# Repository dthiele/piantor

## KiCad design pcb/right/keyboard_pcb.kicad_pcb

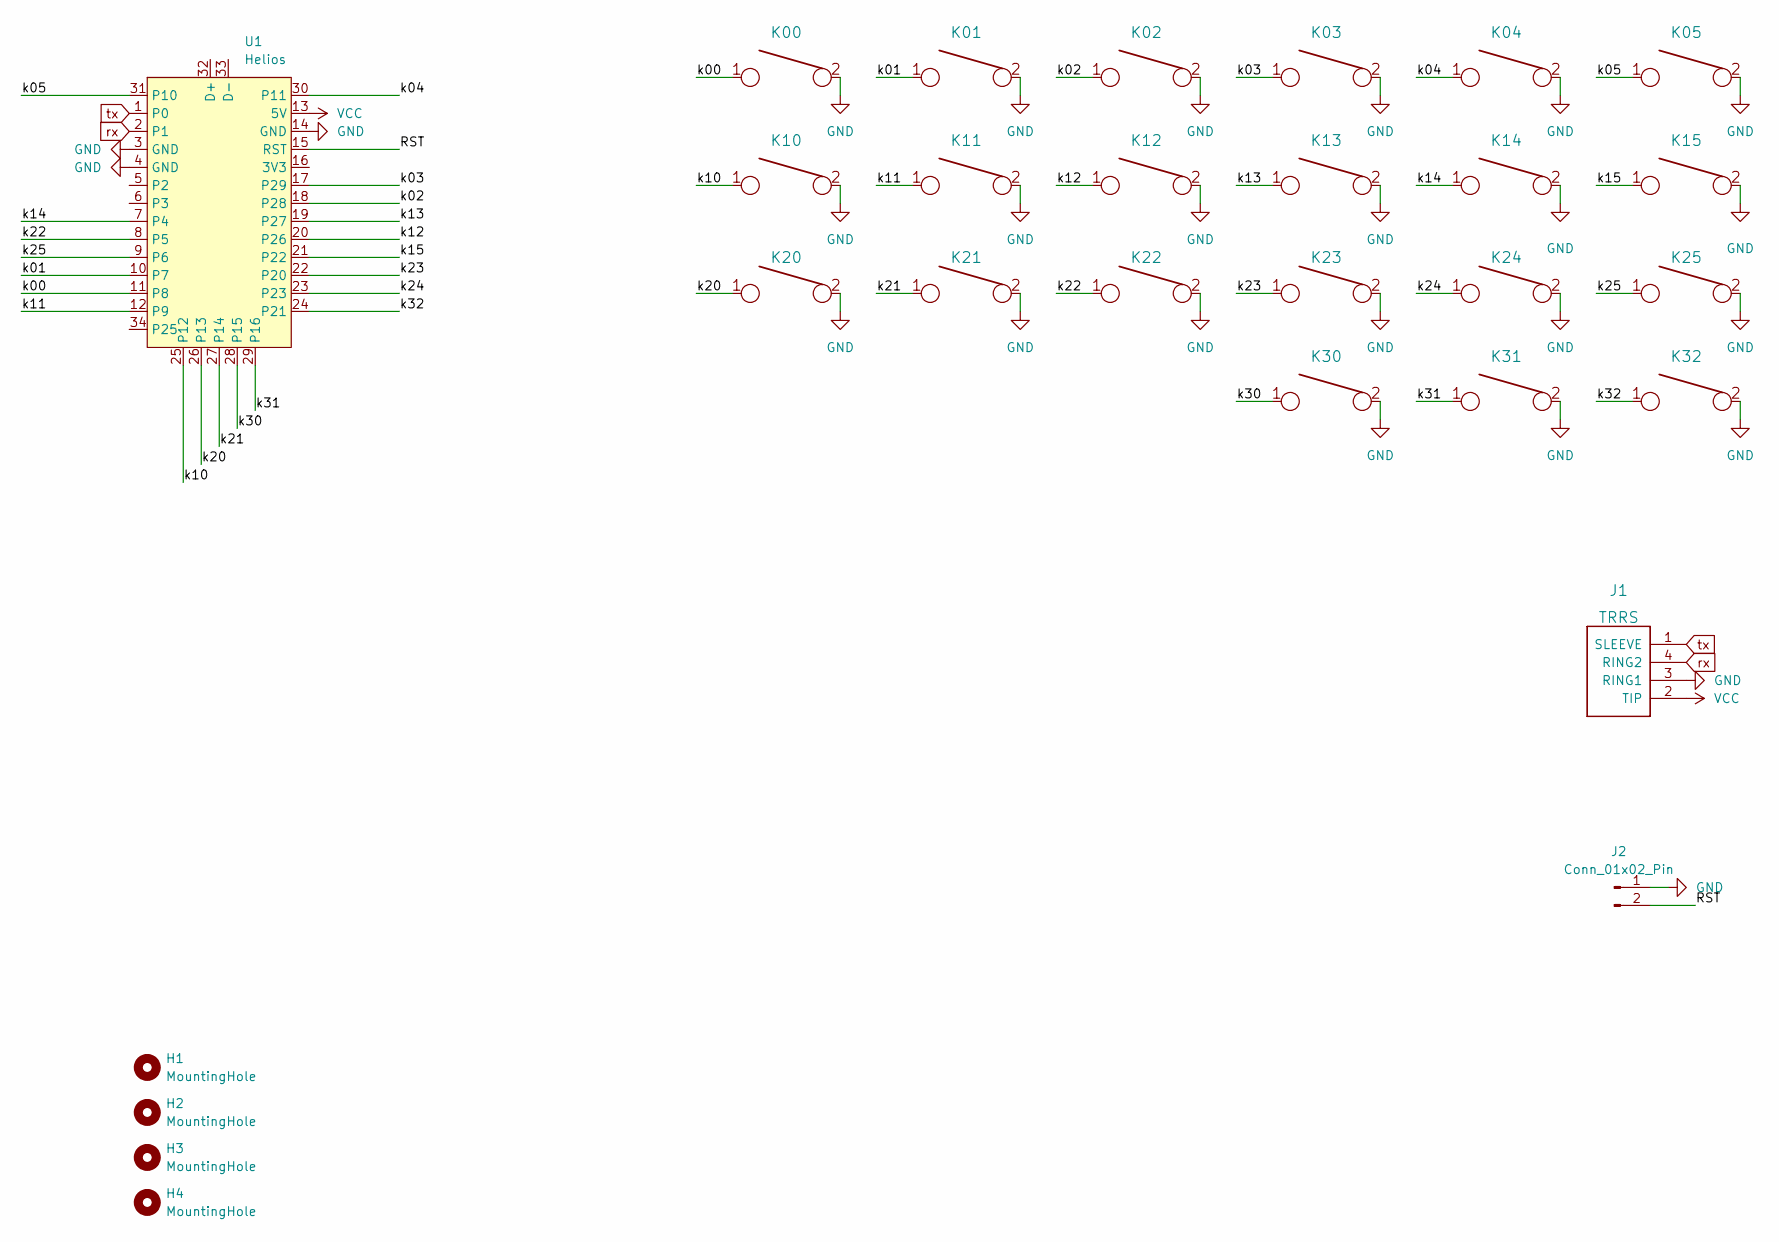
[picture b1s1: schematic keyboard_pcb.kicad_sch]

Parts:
H1, H2, H3, H4: MountingHole; MountingHole_2.2mm_M2-8mm
J1: TRRS; TRRS-PJ-320A
J2: Conn_01x02_Pin; SW_SKHLLCA010
K00, K01, K02, K03, K04, K05, K10, K11, K12, K13, K14, K15, K20, K21, K22, K23, K24, K25, K30, K31, K32: KEYSW; Kailh_socket_PG1350_optional
U1: Helios; Helios_AH_USBdn

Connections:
/RST: J2.2, U1.15 (RST)
/k00: K00.1, U1.11 (P8)
/k01: K01.1, U1.10 (P7)
/k02: K02.1, U1.18 (P28)
/k03: K03.1, U1.17 (P29)
/k04: K04.1, U1.30 (P11)
/k05: K05.1, U1.31 (P10)
/k10: K10.1, U1.25 (P12)
/k11: K11.1, U1.12 (P9)
/k12: K12.1, U1.20 (P26)
/k13: K13.1, U1.19 (P27)
/k14: K14.1, U1.7 (P4)
/k15: K15.1, U1.21 (P22)
/k20: K20.1, U1.26 (P13)
/k21: K21.1, U1.27 (P14)
/k22: K22.1, U1.8 (P5)
/k23: K23.1, U1.22 (P20)
/k24: K24.1, U1.23
/k25: K25.1, U1.9 (P6)
/k30: K30.1, U1.28 (P15)
/k31: K31.1, U1.29 (P16)
/k32: K32.1, U1.24 (P21)
GND: J1.3 (RING1), J2.1, K00.2, K01.2, K02.2, K03.2, K04.2, K05.2, K10.2, K11.2, K12.2, K13.2, K14.2, K15.2, K20.2, K21.2, K22.2, K23.2, K24.2, K25.2, K30.2, K31.2, K32.2, U1.3 (GND), U1.4 (GND), U1.14 (GND)
VCC: J1.2 (TIP), U1.13 (5V)
rx: J1.4 (RING2), U1.2 (P1)
tx: J1.1 (SLEEVE), U1.1 (P0)

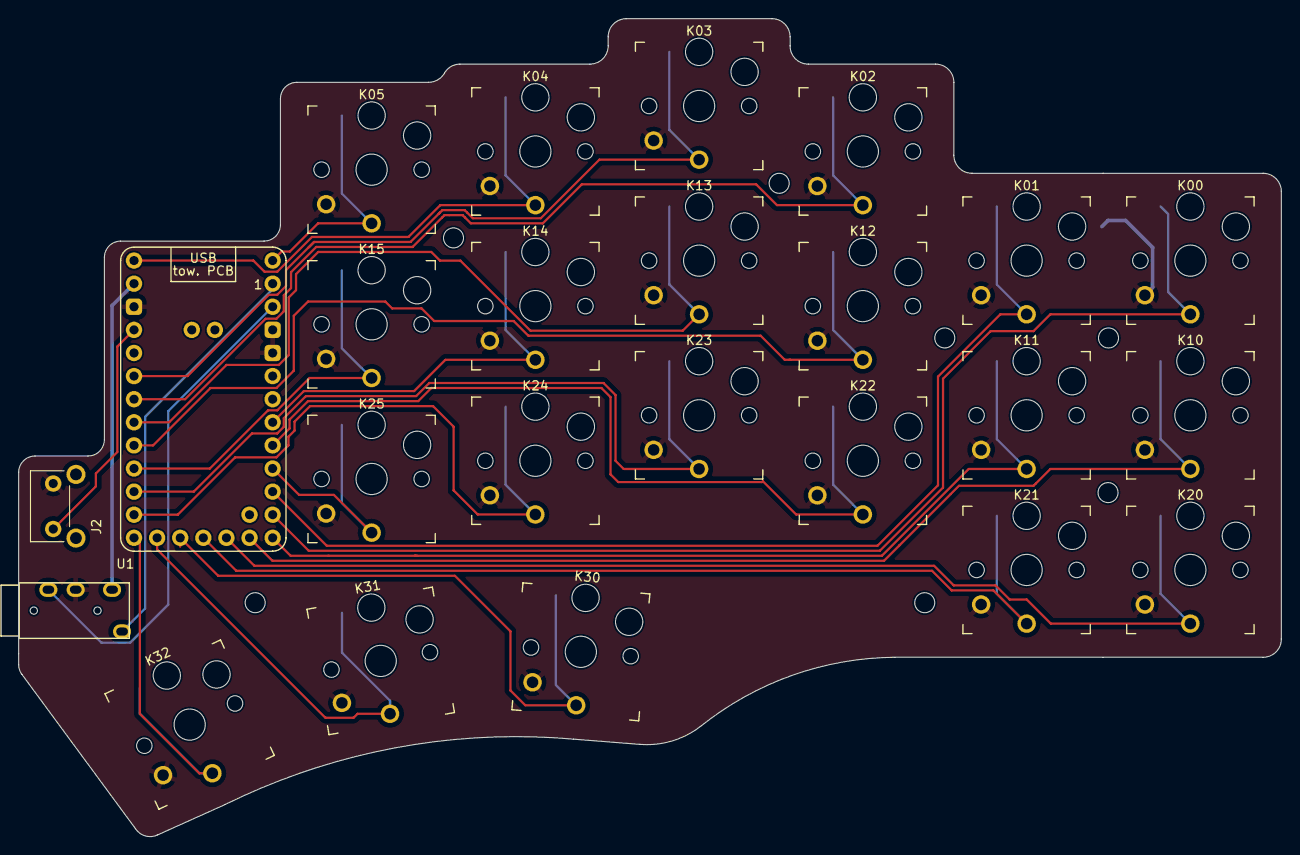
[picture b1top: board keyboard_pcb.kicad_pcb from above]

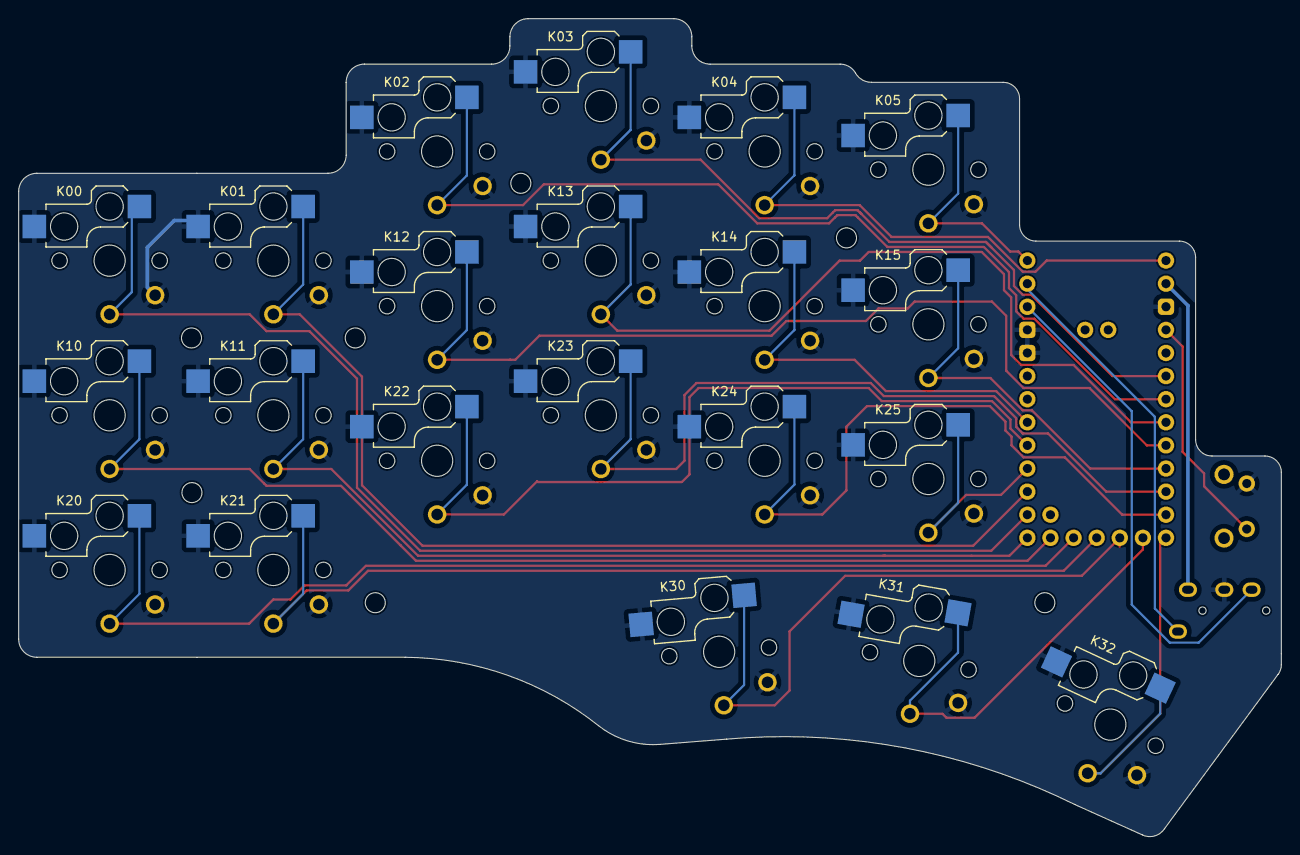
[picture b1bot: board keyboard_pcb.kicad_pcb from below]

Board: 2 copper layers, 138.8 x 89.9 mm, 31 parts (7 on the bottom side), 26 nets.

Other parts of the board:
H1#2, H4#2, H4#3: MountingHole; MountingHole_2.2mm_M2-8mm

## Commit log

2024-09-29 Switched to 0xCB Helios controller
2024-09-29 Adjust PCB outlines
2024-09-29 Add ground plane. Add reset pins.
2024-10-10 Rotate TRRS jack. Replace reset pins by reset button.
2024-10-20 Assigned 3d models
2024-10-20 Update mounting hole position
2025-01-13 Connect missing GND link
